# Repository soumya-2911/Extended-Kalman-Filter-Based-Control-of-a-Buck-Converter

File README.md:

# Extended-Kalman-Filter-Based-Control-of-a-Buck-Converter

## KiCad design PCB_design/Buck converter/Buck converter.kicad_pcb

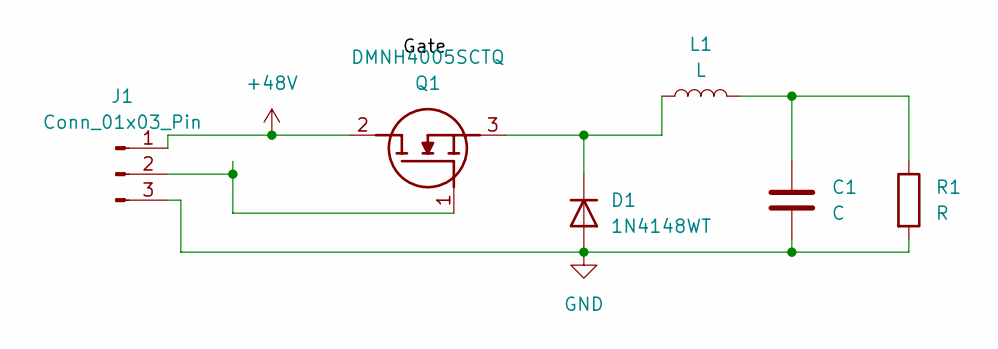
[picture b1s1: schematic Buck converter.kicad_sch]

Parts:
C1: C; C_Axial_L3.8mm_D2.6mm_P7.50mm_Horizontal
D1: 1N4148WT; D_SOD-523
J1: Conn_01x03_Pin; FanPinHeader_1x03_P2.54mm_Vertical
L1: L; L_Axial_L14.5mm_D5.8mm_P20.32mm_Horizontal_Fastron_HBCC
Q1: DMNH4005SCTQ; TO254P482X1016X2221-3P; Manufacturer_Part_Number DMNH4005SCTQ
R1: R; R_Axial_DIN0207_L6.3mm_D2.5mm_P5.08mm_Vertical

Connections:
+48V: J1.1, Q1.2 (D)
GND: C1.2, D1.2 (A), J1.3, R1.2
unnamed: C1.1, L1.2, R1.1
unnamed: D1.1 (K), L1.1, Q1.3 (S)
unnamed: J1.2, Q1.1 (G)

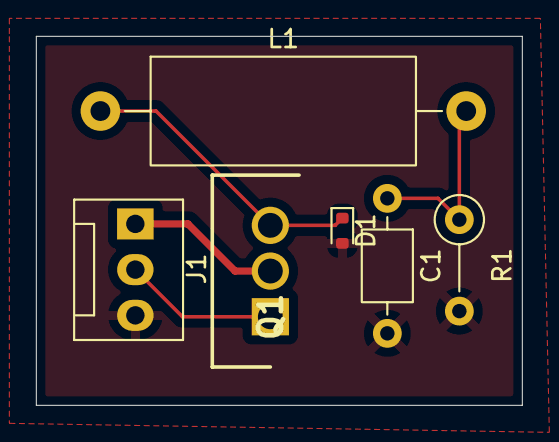
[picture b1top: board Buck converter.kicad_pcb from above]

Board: 4 copper layers, 27.0 x 20.5 mm, 6 parts (0 on the bottom side), 5 nets.
